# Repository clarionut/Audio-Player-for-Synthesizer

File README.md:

# Audio Player for Synthesizer
An audio player for a modular synthesizer based on a cheap 'Kebidu music speakers' module with FM radio, USB, micro SD, Bluetooth and aux-in modes.
This was inspired by the [Tesseract Modular 'Low Coast'](https://www.tesseractmodular.com/eurorack-modules/low-coast/) module which simply provides two Eurorack-level outputs, one for each of the stereo channels of the module.

This version also provides a mono mix output and has trigger inputs for the transport controls - play/pause, next station/track & previous station/track.

I'm not sure that this will be a particularly useful synth module, but I wanted to experiment using FETs as switches to allow external control. Somewhat to my surprise this works perfectly, with the switches being triggered by the rising edge of input pulses. Also the Kebidu units are very cheap - I got two for around £5 including shipping.

### Details
The Schematics folder contains pictures of the kicad schematic, the stripboard layout I used to build the module and a proposed PCB layout. There are several copper-side links (shown in blue) on the stripboard layout including two hard to see ones from pins 8 and 14 of the TL074 to the 100k resistors. Note that I haven't had the PCB fabricated, so use this layout at your own risk! The kicad project itself is in the AudioPlayer folder.

The only tricky part of the build was soldering the source and drain legs of the 2N7000 FETs across the switches. The solder pads are very small, so a fine-tipped soldering iron and a steady hand are needed! I've included a [photo showing the orientation of the FETs](https://github.com/clarionut/Audio-Player-for-Synthesizer/blob/main/pictures/Audio%20Player%20FETs.jpg) on my module. The correct orientation can be checked by measuring the voltage across each switch with a high impedance voltmeter. The drain of the FET is soldered to the more positive end of the switch, source to the negative end and the gate connected to the circuit board with a flying lead.

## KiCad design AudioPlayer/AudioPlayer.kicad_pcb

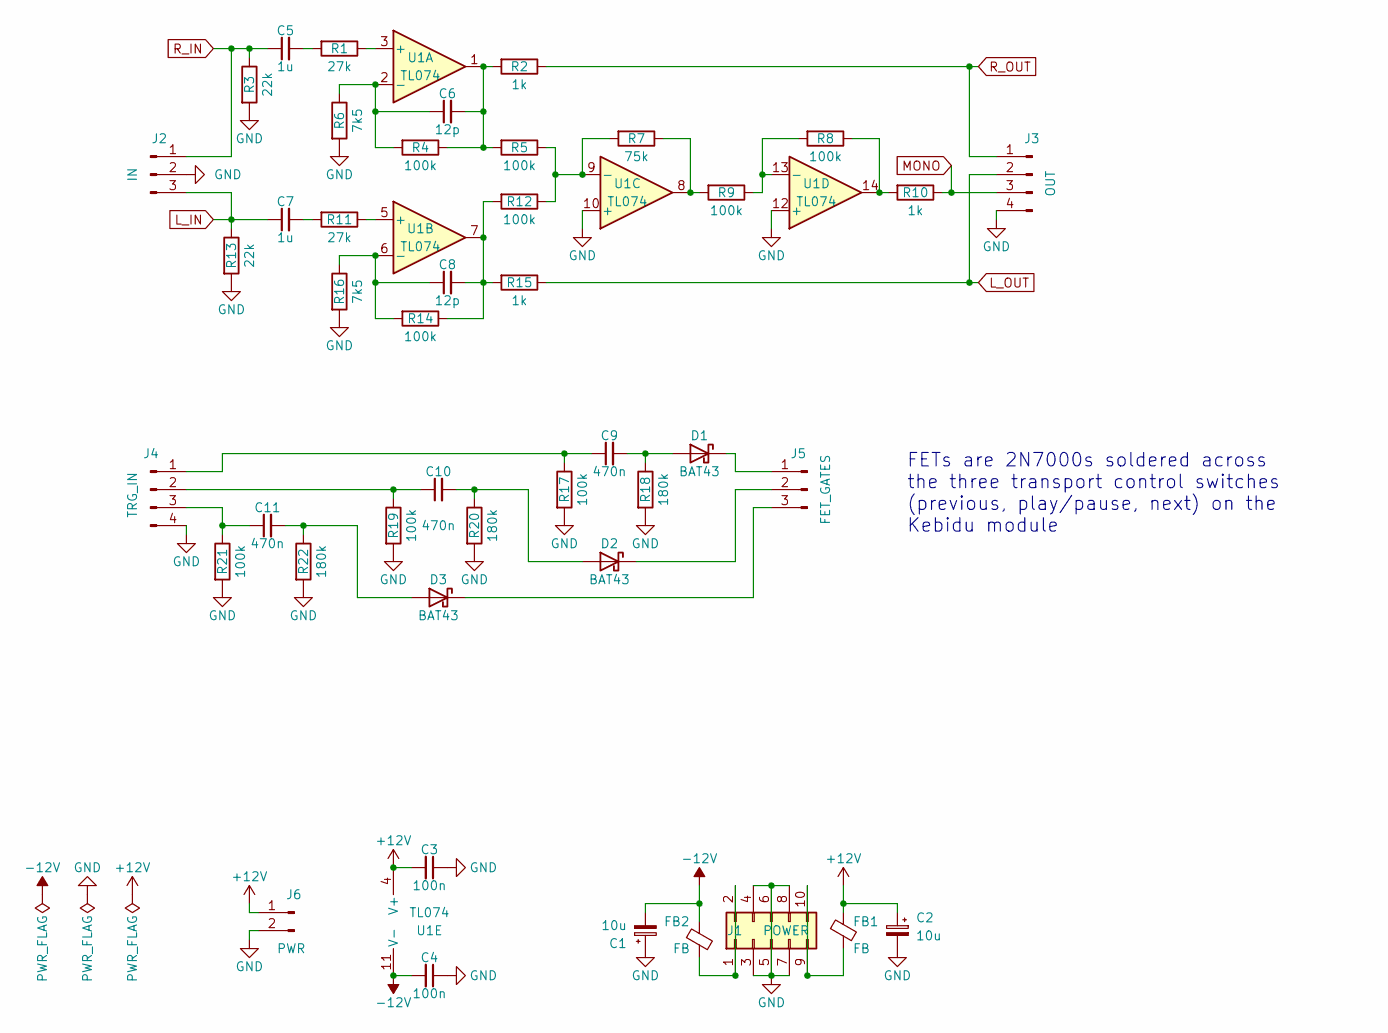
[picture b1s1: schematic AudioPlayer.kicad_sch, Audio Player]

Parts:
C1, C2: 10u; CP_Radial_D5.0mm_P2.50mm
C3, C4: 100n; C_Disc_D4.3mm_W1.9mm_P5.00mm
C5, C7: 1u; C_Rect_L7.0mm_W4.5mm_P5.00mm
C6, C8: 12p; C_Disc_D4.3mm_W1.9mm_P5.00mm
C9, C10, C11: 470n; C_Disc_D4.3mm_W1.9mm_P5.00mm
D1, D2, D3: BAT43; D_DO-35_SOD27_P7.62mm_Horizontal
FB1, FB2: FB; L_Axial_L5.3mm_D2.2mm_P7.62mm_Horizontal_Vishay_IM-1
J1: POWER; Power_2x05
J2: IN; JST_EH_B3B-EH-A_1x03_P2.50mm_Vertical
J3: OUT; PinHeader_1x04_P2.54mm_Vertical
J4: TRG_IN; PinHeader_1x04_P2.54mm_Vertical
J5: FET_GATES; PinHeader_1x03_P2.54mm_Vertical
J6: PWR; JST_EH_B2B-EH-A_1x02_P2.50mm_Vertical
R1, R11: 27k; R_Axial_DIN0204_L3.6mm_D1.6mm_P7.62mm_Horizontal
R2, R10, R15: 1k; R_Axial_DIN0204_L3.6mm_D1.6mm_P7.62mm_Horizontal
R3, R13: 22k; R_Axial_DIN0204_L3.6mm_D1.6mm_P7.62mm_Horizontal
R4, R5, R8, R9, R12, R14, R17, R19, R21: 100k; R_Axial_DIN0204_L3.6mm_D1.6mm_P7.62mm_Horizontal
R6, R16: 7k5; R_Axial_DIN0204_L3.6mm_D1.6mm_P7.62mm_Horizontal
R7: 75k; R_Axial_DIN0204_L3.6mm_D1.6mm_P7.62mm_Horizontal
R18, R20, R22: 180k; R_Axial_DIN0204_L3.6mm_D1.6mm_P7.62mm_Horizontal
U1: TL074; DIP-14_W7.62mm_Socket

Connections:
+12V: C2.1, C3.2, FB1.1, J6.1, U1.4 (V+)
-12V: C1.2, C4.2, FB2.1, U1.11 (V-)
GND: C1.1, C2.2, C3.1, C4.1, J1.3, J1.4, J1.5, J1.6, J1.7, J1.8, J2.2, J3.4, J4.4, J6.2, R3.2, R6.2, R13.2, R16.2, R17.2, R18.2, R19.2, R20.2, R21.2, R22.2, U1.10 (+), U1.12 (+)
L_IN: C7.1, J2.3, R13.1
L_OUT: J3.2, R15.1
MONO: J3.3, R10.1
unnamed: C5.2, R1.2
unnamed: C6.2, R2.2, R4.1, R5.2, U1.1
unnamed: C7.2, R11.2
unnamed: C8.2, R12.2, R14.1, R15.2, U1.7
unnamed: C9.2, D1.2 (A), R18.1
unnamed: D1.1 (K), J5.1
unnamed: C10.2, D2.2 (A), R20.1
unnamed: D2.1 (K), J5.2
unnamed: C11.2, D3.2 (A), R22.1
unnamed: D3.1 (K), J5.3
unnamed: FB2.2, J1.1, J1.2
unnamed: FB1.2, J1.9, J1.10
unnamed: C9.1, J4.1, R17.1
unnamed: C10.1, J4.2, R19.1
unnamed: C11.1, J4.3, R21.1
unnamed: R7.1, R9.2, U1.8
unnamed: R8.1, R10.2, U1.14
unnamed: R1.1, U1.3 (+)
unnamed: C6.1, R4.2, R6.1, U1.2 (-)
unnamed: R11.1, U1.5 (+)
unnamed: C8.1, R14.2, R16.1, U1.6 (-)
unnamed: R5.1, R7.2, R12.1, U1.9 (-)
unnamed: R8.2, R9.1, U1.13 (-)
R_IN: C5.1, J2.1, R3.1
R_OUT: J3.1, R2.1

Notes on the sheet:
FETs are 2N7000s soldered across the three transport control switches (previous, play/pause, next) on the Kebidu module

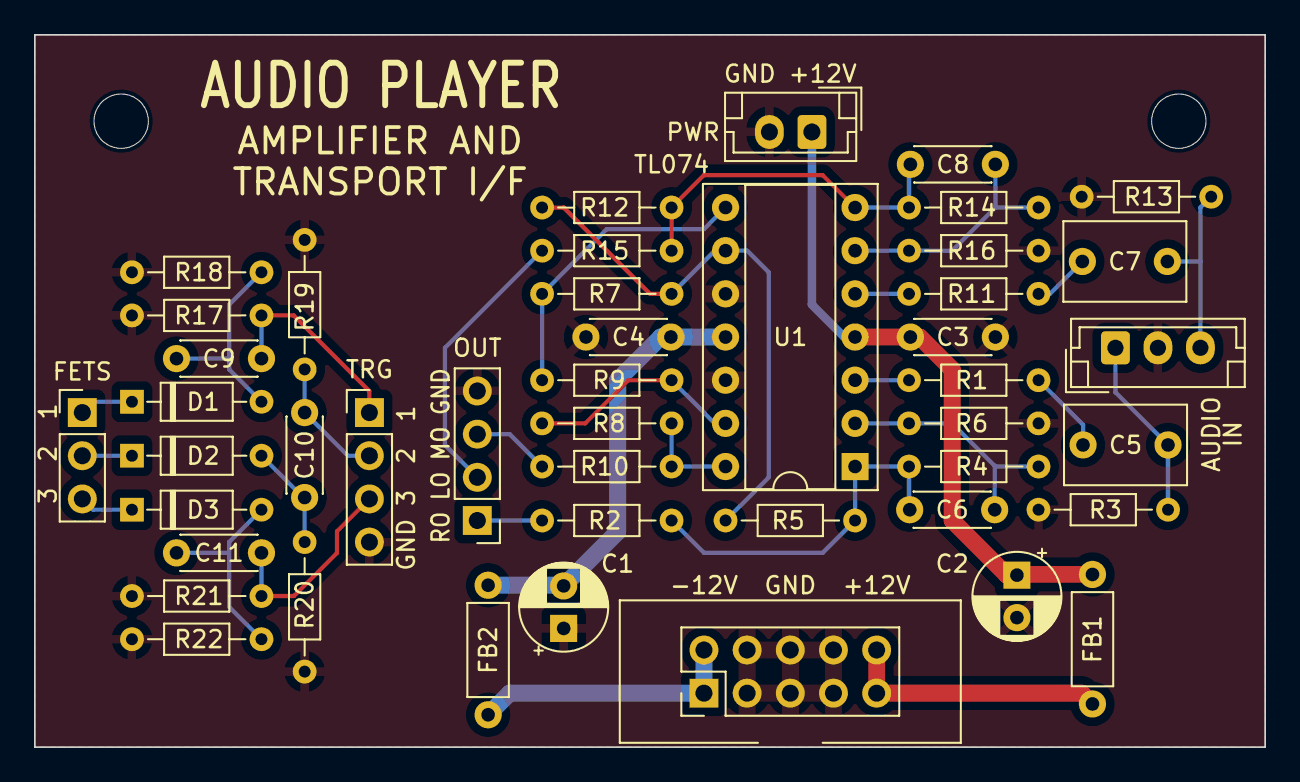
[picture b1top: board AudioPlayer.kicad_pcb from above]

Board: 2 copper layers, 72.4 x 41.9 mm, 45 parts (0 on the bottom side), 31 nets.

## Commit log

2025-09-03 Create README.md
    Audio Player for Synthesizer based on a cheap audio module
2025-09-03 Create tmp
